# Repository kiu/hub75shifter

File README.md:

# hub75shifter
Modular ticker display

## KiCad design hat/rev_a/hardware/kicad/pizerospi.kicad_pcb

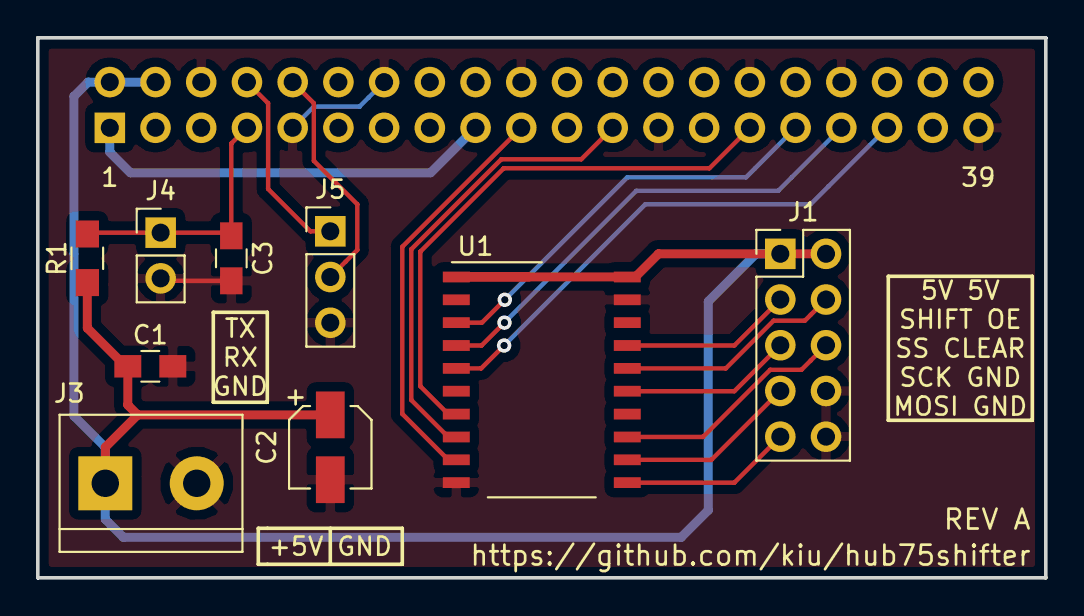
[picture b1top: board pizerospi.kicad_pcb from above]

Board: 2 copper layers, 56.0 x 30.0 mm, 10 parts (1 on the bottom side), 18 nets.

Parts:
C1, C3: 100nF; C_0805_HandSoldering
C2: 100uF; CP_Elec_4x5.7
J1: Conn_02x05_Odd_Even; Pin_Header_Straight_2x05_Pitch2.54mm
J2: Conn_02x20_Odd_Even; Socket_Strip_Straight_2x20_Pitch2.54mm
J3: Screw_Terminal_01x02; TerminalBlock_bornier-2_P5.08mm
J4: Conn_01x02; Pin_Header_Straight_1x02_Pitch2.54mm
J5: Conn_01x03; Pin_Header_Straight_1x03_Pitch2.54mm
R1: R; R_0805_HandSoldering
U1: 74HC245; SO-20_12.8x7.5mm_Pitch1.27mm

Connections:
H75_CLEAR: J1.5, U1.15
H75_MOSI: J1.9, U1.11
H75_OE: J1.4, U1.16
H75_SCK: J1.7, U1.12
H75_SHIFT: J1.3, U1.17
H75_SS: J1.6, U1.13
PI_3V3: J2.1, J2.17
PI_5V: C1.1, C2.1, J1.1, J1.2, J2.2, J2.4, J3.1, R1.1, U1.1, U1.20
PI_GND: C1.2, C2.2, C3.2, J1.8, J1.10, J2.6, J2.9, J2.14, J2.20, J2.25, J2.30, J2.34, J2.39, J3.2, J4.2, J5.3, U1.10, U1.19
PI_GPIO_04: C3.1, J2.7, J4.1, R1.2
PI_GPIO_05: J2.29, U1.7
PI_GPIO_06: J2.31, U1.3
PI_GPIO_10_MOSI: J2.19, U1.9
PI_GPIO_11_SCLK: J2.23, U1.8
PI_GPIO_13: J2.33, U1.4
PI_GPIO_14_TXD: J2.8, J5.1
PI_GPIO_15_RXD: J2.10, J5.2
PI_GPIO_19: J2.35, U1.5

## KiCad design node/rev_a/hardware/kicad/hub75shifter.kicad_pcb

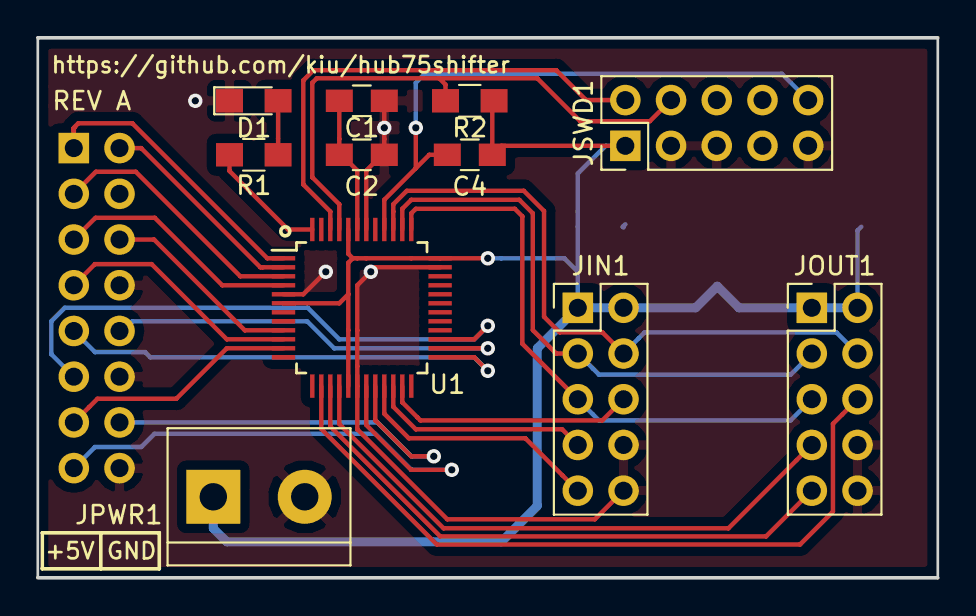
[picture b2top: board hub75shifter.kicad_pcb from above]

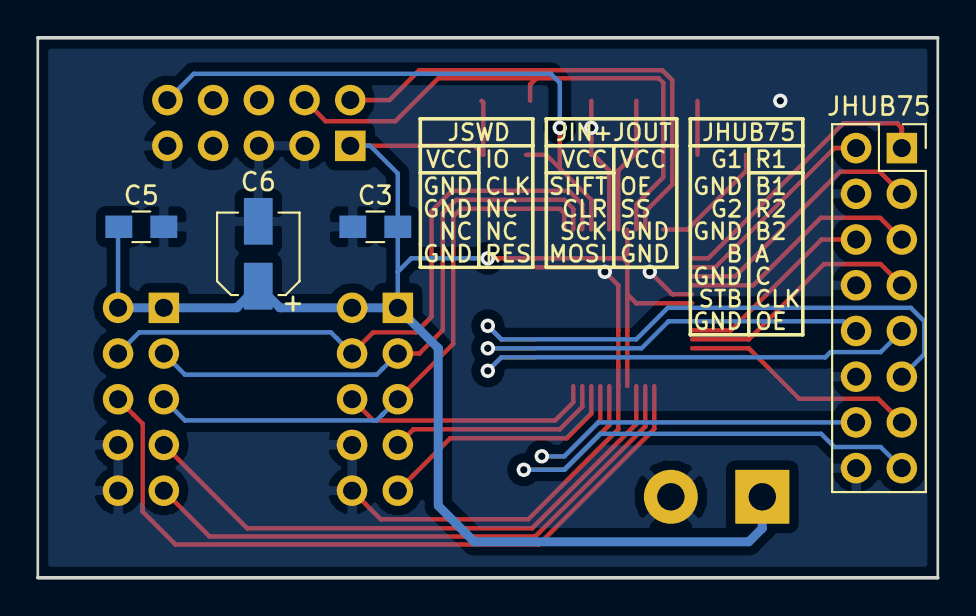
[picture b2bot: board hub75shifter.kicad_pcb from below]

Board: 2 copper layers, 50.0 x 30.0 mm, 15 parts (4 on the bottom side), 29 nets.

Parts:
C1, C3, C5: 100nF; C_0805_HandSoldering
C2: 1uF; C_0805_HandSoldering
C4: 100pF; C_0805_HandSoldering
C6: 10uF; CP_Elec_4x5.7
D1: LED; LED_0805_HandSoldering
JHUB75: Conn_02x08_Odd_Even; Socket_Strip_Straight_2x08_Pitch2.54mm
JIN1: Conn_02x05_Odd_Even; Pin_Header_Straight_2x05_Pitch2.54mm
JOUT1: Conn_02x05_Odd_Even; Pin_Header_Straight_2x05_Pitch2.54mm
JPWR1: Screw_Terminal_01x02; TerminalBlock_bornier-2_P5.08mm
JSWD1: Conn_02x05_Odd_Even; Pin_Header_Straight_2x05_Pitch2.54mm
R1: 60R; R_0805_HandSoldering
R2: 1k; R_0805_HandSoldering
U1: SAMC20G17A-A; TQFP-48_7x7mm_Pitch0.5mm

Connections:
CLEAR: JIN1.5, JOUT1.5, U1.37
GND: C1.2, C2.2, C3.2, C5.2, C6.2, D1.1, JHUB75.4, JHUB75.8, JHUB75.12, JHUB75.16, JIN1.8, JIN1.10, JOUT1.8, JOUT1.10, JPWR1.2, JSWD1.3, JSWD1.5, JSWD1.9, U1.5, U1.18, U1.35, U1.42
LED: R1.2, U1.48
MCU_RESET: C4.2, JSWD1.10, U1.40
unnamed: C1.1, C2.1, U1.43
unnamed: D1.2, R1.1
OE: JIN1.4, JOUT1.4, U1.39
P_A: JHUB75.9, U1.25
P_B: JHUB75.10, U1.26
P_B1: JHUB75.3, U1.3
P_B2: JHUB75.7, U1.10
P_C: JHUB75.11, U1.27
P_CLK: JHUB75.13, U1.11
P_G1: JHUB75.2, U1.2
P_G2: JHUB75.6, U1.9
P_OE: JHUB75.15, U1.19
P_R1: JHUB75.1, U1.1
P_R2: JHUB75.5, U1.4
P_STB: JHUB75.14, U1.20
SHIFT: JIN1.3, JOUT1.3, U1.38
SPI0_MOSI: JOUT1.9, U1.15
SPI0_SCK: JOUT1.7, U1.16
SPI0_SS: JOUT1.6, U1.14
SPI1_MOSI: JIN1.9, U1.21
SPI1_SCK: JIN1.7, U1.22
SPI1_SS: JIN1.6, U1.23
SWDCLK: JSWD1.4, R2.2, U1.45
SWDIO: JSWD1.2, U1.46
VCC: C3.1, C4.1, C5.1, C6.1, JIN1.1, JIN1.2, JOUT1.1, JOUT1.2, JPWR1.1, JSWD1.1, R2.1, U1.6, U1.17, U1.36, U1.44

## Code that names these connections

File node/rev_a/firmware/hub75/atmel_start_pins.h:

/*
 * Code generated from Atmel Start.
 *
 * This file will be overwritten when reconfiguring your Atmel Start project.
 * Please copy examples or other code you want to keep to a separate file
 * to avoid losing it when reconfiguring.
 */
#ifndef ATMEL_START_PINS_H_INCLUDED
#define ATMEL_START_PINS_H_INCLUDED

#include <hal_gpio.h>

// SAMC21 has 9 pin functions

#define GPIO_PIN_FUNCTION_A 0
#define GPIO_PIN_FUNCTION_B 1
#define GPIO_PIN_FUNCTION_C 2
#define GPIO_PIN_FUNCTION_D 3
#define GPIO_PIN_FUNCTION_E 4
#define GPIO_PIN_FUNCTION_F 5
#define GPIO_PIN_FUNCTION_G 6
#define GPIO_PIN_FUNCTION_H 7
#define GPIO_PIN_FUNCTION_I 8

#define P_R1 GPIO(GPIO_PORTA, 0)
#define P_G1 GPIO(GPIO_PORTA, 1)
#define P_B1 GPIO(GPIO_PORTA, 2)
#define P_R2 GPIO(GPIO_PORTA, 3)
#define P_G2 GPIO(GPIO_PORTA, 4)
#define P_B2 GPIO(GPIO_PORTA, 5)
#define P_CLK GPIO(GPIO_PORTA, 6)
#define PA08 GPIO(GPIO_PORTA, 8)
#define SPI0_SS GPIO(GPIO_PORTA, 9)
#define PA10 GPIO(GPIO_PORTA, 10)
#define PA11 GPIO(GPIO_PORTA, 11)
#define PA12 GPIO(GPIO_PORTA, 12)
#define PA13 GPIO(GPIO_PORTA, 13)
#define PA14 GPIO(GPIO_PORTA, 14)
#define PA15 GPIO(GPIO_PORTA, 15)
#define P_A GPIO(GPIO_PORTA, 16)
#define P_B GPIO(GPIO_PORTA, 17)
#define P_C GPIO(GPIO_PORTA, 18)
#define OE GPIO(GPIO_PORTA, 27)
#define LED GPIO(GPIO_PORTB, 3)
#define P_OE GPIO(GPIO_PORTB, 10)
#define P_STB GPIO(GPIO_PORTB, 11)
#define CLEAR GPIO(GPIO_PORTB, 22)
#define SHIFT GPIO(GPIO_PORTB, 23)

#endif // ATMEL_START_PINS_H_INCLUDED

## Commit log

2019-11-23 init
2022-05-20 Bump gson from 2.8.6 to 2.8.9 in /hat/server/Hub75Shifter
    Bumps [gson](https://github.com/google/gson) from 2.8.6 to 2.8.9.
    - [Release notes](https://github.com/google/gson/releases)
    - [Changelog](https://github.com/google/gson/blob/master/CHANGELOG.md)
    - [Commits](https://github.com/google/gson/compare/gson-parent-2.8.6...gson-parent-2.8.9)
    ---
    updated-dependencies:
